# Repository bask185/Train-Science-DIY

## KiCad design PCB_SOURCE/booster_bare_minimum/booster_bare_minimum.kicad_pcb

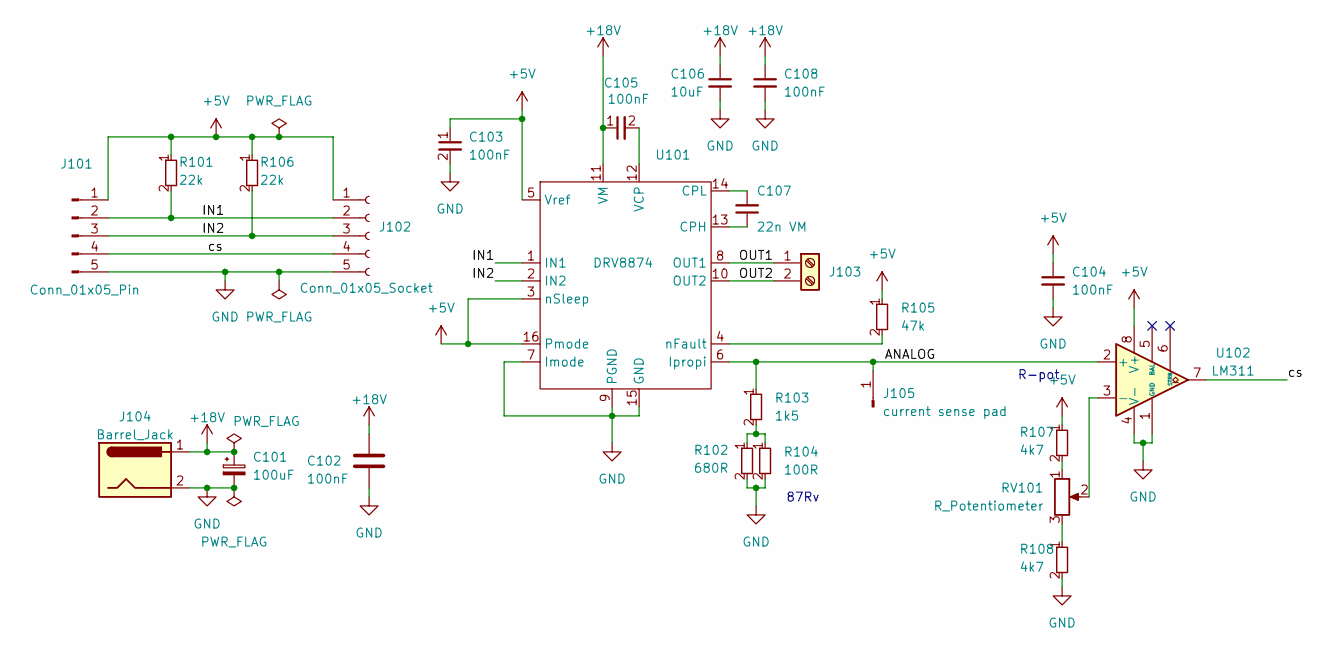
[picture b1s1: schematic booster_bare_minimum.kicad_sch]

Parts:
C101: 100uF; CP_Elec_6.3x5.9; JLCPCB Part# C494840
C102: 100nF; C_0603_1608Metric_Pad1.08x0.95mm_HandSolder; JLCPCB Part# C14663
C103, C105: 100nF; C_0603_1608Metric; JLCPCB Part# C14663
C104, C108: 100nF; C_0402_1005Metric_Pad0.74x0.62mm_HandSolder; LCSC Part # C307331
C106: 10uF; C_1206_3216Metric; LCSC Part # C13585
C107: 22n VM; C_0402_1005Metric_Pad0.74x0.62mm_HandSolder; LCSC Part # C1532
J101: Conn_01x05_Pin; PinHeader_1x05_P2.54mm_Horizontal
J102: Conn_01x05_Socket; PinSocket_1x05_P2.54mm_Horizontal
J103: Screw_Terminal_01x02; PhoenixContact_MC_1,5_2-G-3.5_1x02_P3.50mm_Horizontal; JLCPCB Part# C2840336
J104: Barrel_Jack; BarrelJack_GCT_DCJ200-10-A_Horizontal; JLCPCB Part# C7428747
J105: current sense pad; SolderWirePad_1x01_SMD_1x2mm
R101, R106: 22k; R_0603_smalltext; JLCPCB Part# C31850
R102: 680R; R_0603_smalltext; JLCPCB Part# C17798
R103: 1k5; R_0603_smalltext; JLCPCB Part# C22843
R104: 100R; R_0603_smalltext; JLCPCB Part# C22775
R105: 47k; R_0603_smalltext; JLCPCB Part# C25819
R107, R108: 4k7; R_0603_smalltext; JLCPCB Part# C23162
RV101: R_Potentiometer; Potentiometer_Bourns_TC33X_Vertical; JLCPCB Part# C145161
U101: DRV8874; HTSSOP-16-1EP_4.4x5mm_P0.65mm_EP3.4x5mm; JLCPCB Part# C1855818
U102: LM311; SOP-8_3.9x4.9mm_P1.27mm; JLCPCB Part# C434495

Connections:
+5V: C103.1, C104.1, J101.1, J102.1, R101.1, R105.1, R106.1, R107.1, U101.3 (nSleep), U101.5 (Vref), U101.16 (Pmode), U102.8 (V+)
+18V: C101.1, C102.2, C105.1, C106.1, C108.1, J104.1, U101.11 (VM)
/ANALOG: J105.1, R103.1, U101.6 (Ipropi), U102.2 (+)
/IN1: J101.2, J102.2, R101.2, U101.1 (IN1)
/IN2: J101.3, J102.3, R106.2, U101.2 (IN2)
/OUT1: J103.1, U101.8 (OUT1)
/OUT2: J103.2, U101.10 (OUT2)
/cs: J101.4, J102.4, U102.7
GND: C101.2, C102.1, C103.2, C104.2, C106.2, C108.2, J101.5, J102.5, J104.2, R102.2, R104.2, R108.2, U101.7 (Imode), U101.9 (PGND), U101.15 (GND), U101.17 (GND), U102.1 (GND), U102.4 (V-)
unnamed: R102.1, R103.2, R104.1
unnamed: R107.2, RV101.1
unnamed: R108.1, RV101.3
unnamed: C107.1, U101.13 (CPH)
unnamed: C107.2, U101.14 (CPL)
unnamed: C105.2, U101.12 (VCP)
unnamed: R105.2, U101.4 (nFault)
unnamed: RV101.2, U102.3 (-)

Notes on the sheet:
87Rv
R-pot

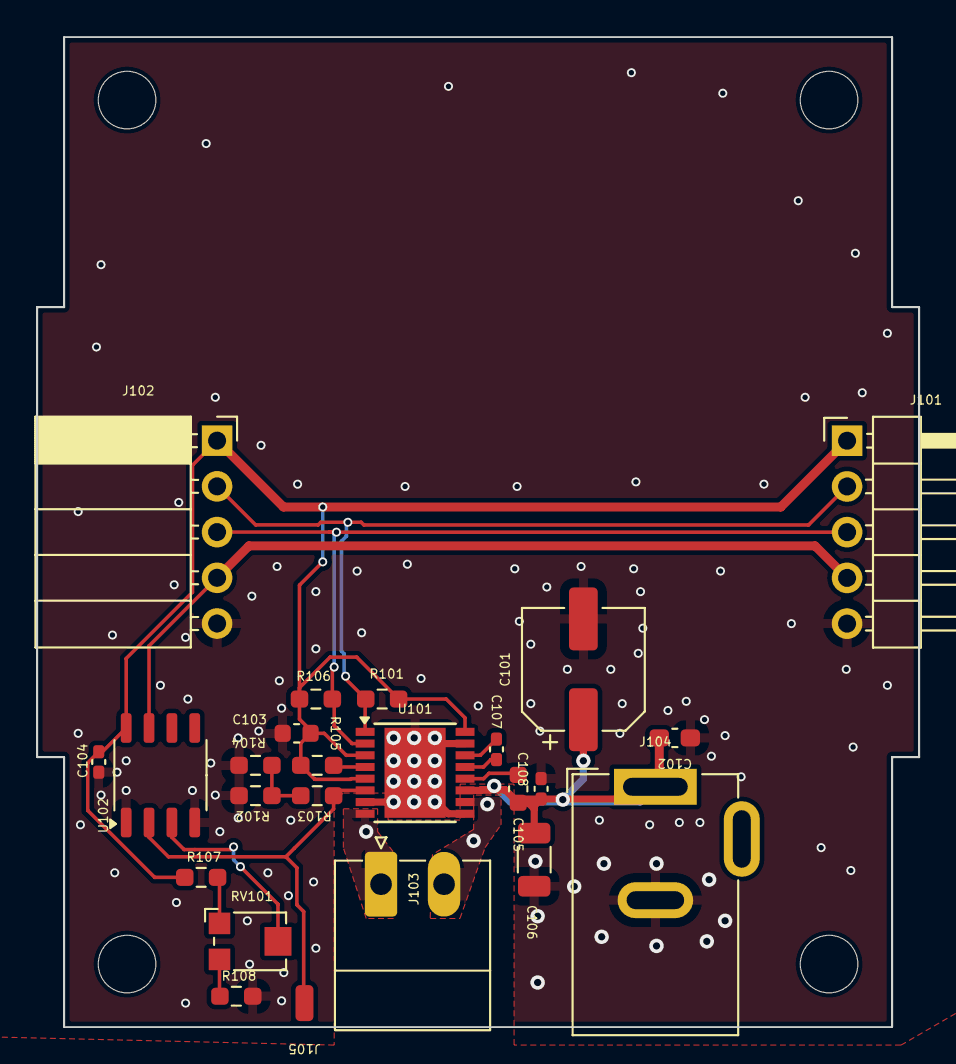
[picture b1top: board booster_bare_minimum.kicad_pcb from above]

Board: 2 copper layers, 49.0 x 55.0 mm, 24 parts (0 on the bottom side), 17 nets.

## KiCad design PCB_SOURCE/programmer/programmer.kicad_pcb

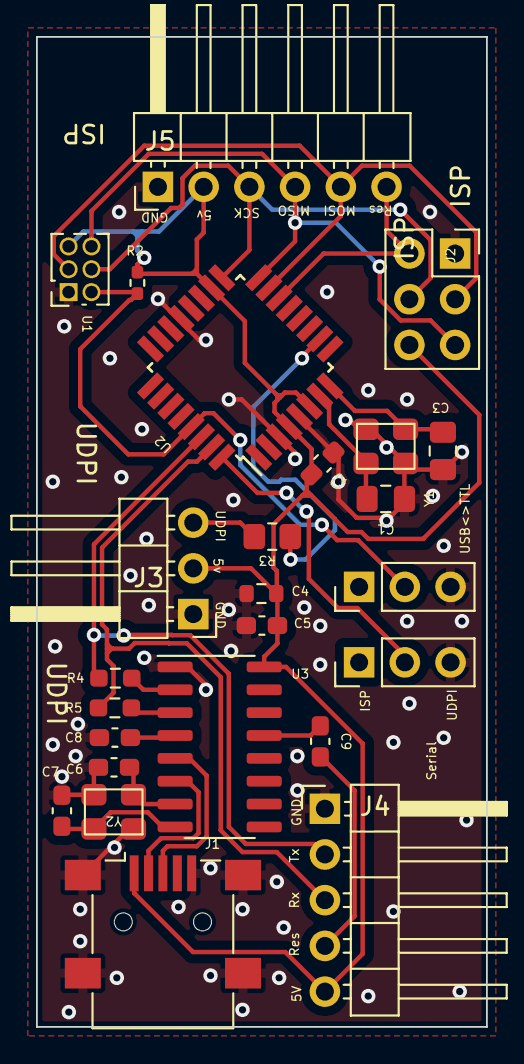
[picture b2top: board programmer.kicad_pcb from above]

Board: 2 copper layers, 25.0 x 55.0 mm, 25 parts (0 on the bottom side), 23 nets.

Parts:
C1, C3: 12pF; C_0805_2012Metric_Pad1.18x1.45mm_HandSolder
C2, C5, C8, C9: 100nF; C_0603_1608Metric_Pad1.08x0.95mm_HandSolder
C4: 10uF; R_0603_1608Metric
C6, C7: 22pF; C_0603_1608Metric_Pad1.08x0.95mm_HandSolder
J1: USB_B_Mini; USB_Mini-B_Lumberg_2486_01_Horizontal
J2: 2x3 ISP; PinSocket_2x03_P2.54mm_Vertical
J3: UDPI; PinHeader_1x03_P2.54mm_Horizontal
J4: USB_TTL; PinHeader_1x05_P2.54mm_Horizontal
J5: 1x6 ISP; PinHeader_1x06_P2.54mm_Horizontal
R2: 10k; R_0402_1005Metric_Pad0.72x0.64mm_HandSolder
R3: 4k7; R_0805_handsolder-smalltext
R4, R5: 1k; R_0603_1608Metric_Pad0.98x0.95mm_HandSolder
SW2, SW101: SW_SPDT; PinHeader_1x03_P2.54mm_Vertical
U1: HEADER_3x2; PinSocket_2x03_P1.27mm_Vertical
U2: ATmega328-A; TQFP-32_7x7mm_P0.8mm
U3: CH340G; SOIC-16_3.9x9.9mm_P1.27mm
Y1: Crystal_GND2; crystal_arduino
Y2: Crystal; crystal_arduino

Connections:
+5V: C2.2, C4.1, C5.1, J1.1 (VBUS), J2.6, J3.2, J4.5, J5.2, R2.1, U1.5, U2.4 (VCC), U2.6 (VCC), U2.18 (AVCC), U3.16 (VCC)
/MISO: J2.5, J5.4, U1.6, U2.16 (PB4)
/MOSI: J2.3, J5.5, U1.3, U2.15 (PB3)
/RESET: J2.2, J5.6, U2.14 (PB2)
/RX: J4.2, R4.2, U2.30 (PD0)
/SCK: J2.4, J5.3, U1.4, U2.17 (PB5)
/TX: J4.3, R5.1, U2.31 (PD1)
/UDPI: J3.3, R3.2
/USB_RESET: C9.2, J4.4
/X1: C1.2, U2.7 (XTAL1/PB6), Y1.1
/X2: C3.2, U2.8 (XTAL2/PB7), Y1.3
/our_reset: R2.2, SW101.2 (B), U1.2, U2.29 (~RESET/PC6)
GND: C1.1, C2.1, C3.1, C4.2, C5.2, C6.2, C7.2, C8.1, J1.5 (GND), J1.6 (Shield), J2.1, J3.1, J4.1, J5.1, SW2.3 (C), SW101.3 (C), U1.1, U2.3 (GND), U2.5 (GND), U2.21 (GND), U3.1 (GND), Y1.2 (GND), Y1.4 (GND), Y2.2 (GND), Y2.4 (GND)
unnamed: J1.3 (D+), U3.5 (UD+)
unnamed: J1.2 (D-), U3.6 (UD-)
unnamed: SW2.2 (B), U2.32 (PD2)
unnamed: R3.1, U2.10 (PD6)
unnamed: R5.2, U3.3 (RXD)
unnamed: R4.1, U3.2 (TXD)
unnamed: C8.2, U3.4 (V3)
unnamed: C6.1, U3.7 (XI), Y2.1
unnamed: C7.1, U3.8 (XO), Y2.3
unnamed: C9.1, U3.13 (~DTR)

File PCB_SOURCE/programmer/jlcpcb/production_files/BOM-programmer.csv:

Comment,Designator,Footprint,LCSC
Crystal_GND2,Y1,crystal_arduino,C13738
CH340G,U3,SOIC-16_3.9x9.9mm_P1.27mm,C14267
100nF,"C2,C5,C8,C9",C_0603_1608Metric_Pad1.08x0.95mm_HandSolder,C14663
ATmega328-A,U2,TQFP-32_7x7mm_P0.8mm,C14877
22pF,"C6,C7",C_0603_1608Metric_Pad1.08x0.95mm_HandSolder,C1653
4k7,R3,R_0805_handsolder-smalltext,C17673
12pF,C3,C_0805_2012Metric_Pad1.18x1.45mm_HandSolder,C1792
1k,"R4,R5",R_0603_1608Metric_Pad0.98x0.95mm_HandSolder,C21190
10k,R2,R_0402_1005Metric_Pad0.72x0.64mm_HandSolder,C25744
USB_B_Mini,J1,USB_Mini-B_Lumberg_2486_01_Horizontal,C2681563
Crystal,Y2,crystal_arduino,C9002
10uF,C4,R_0603_1608Metric,C96446
SW_SPDT,SW101,PinHeader_1x03_P2.54mm_Vertical,
SW_SPDT,SW2,PinHeader_1x03_P2.54mm_Vertical,
HEADER_3x2,U1,PinSocket_2x03_P1.27mm_Vertical,
1x6 ISP,J5,PinHeader_1x06_P2.54mm_Horizontal,
12pF,C1,C_0805_2012Metric_Pad1.18x1.45mm_HandSolder,
UDPI,J3,PinHeader_1x03_P2.54mm_Horizontal,
2x3 ISP,J2,PinSocket_2x03_P2.54mm_Vertical,
USB_TTL,J4,PinHeader_1x05_P2.54mm_Horizontal,

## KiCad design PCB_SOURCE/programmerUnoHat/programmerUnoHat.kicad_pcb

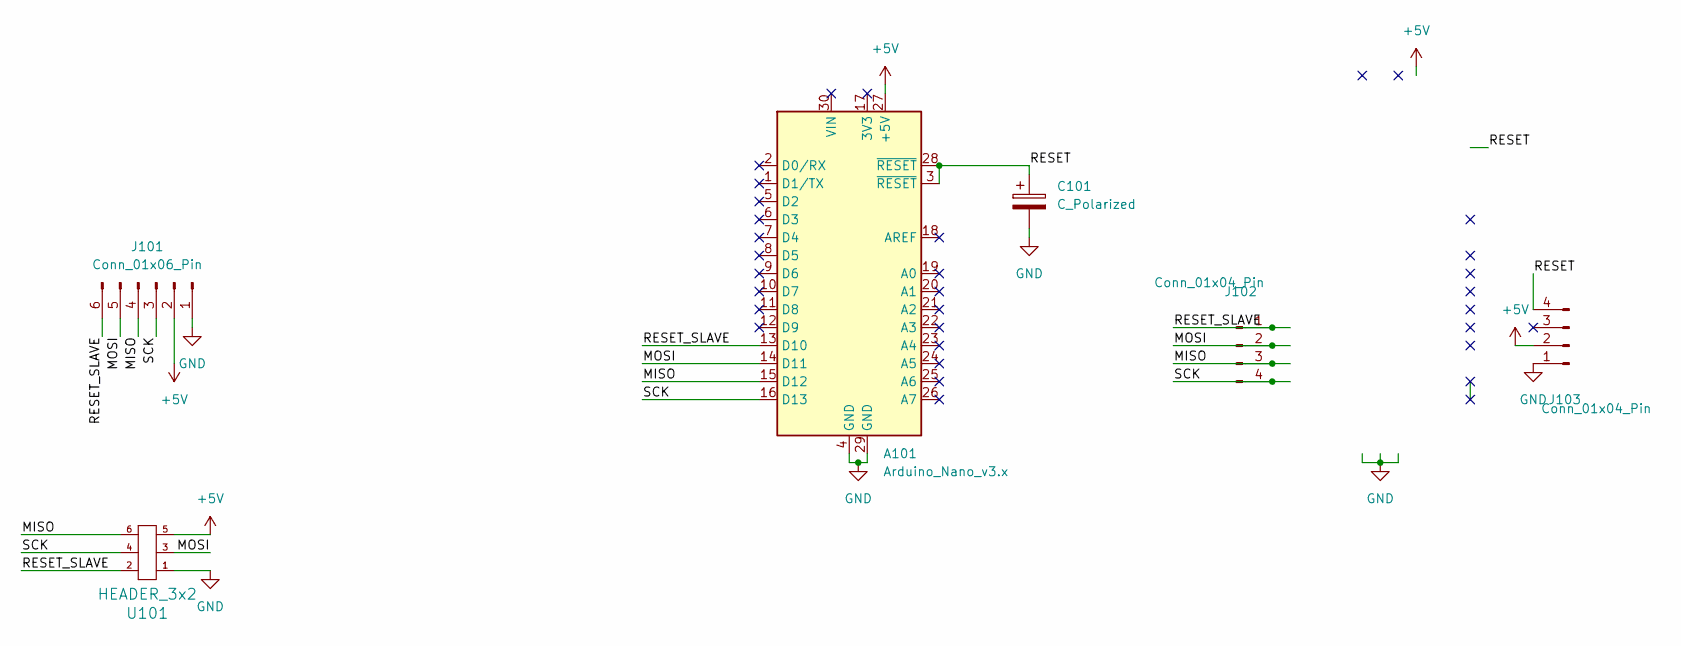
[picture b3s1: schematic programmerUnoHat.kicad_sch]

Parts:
A101: Arduino_Nano_v3.x; Arduino_Nano
C101: C_Polarized; CP_Radial_D6.3mm_P2.50mm
J101: Conn_01x06_Pin; PinHeader_1x06_P2.54mm_Vertical
J102, J103: Conn_01x04_Pin; PinHeader_1x04_P2.54mm_Vertical
U101: HEADER_3x2; PinSocket_2x03_P1.27mm_Vertical

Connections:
+5V: A101.27 (+5V), J101.2, J103.2, U101.5
/MISO: A101.15 (D12), J101.4, J102.3, U101.6
/MOSI: A101.14 (D11), J101.5, J102.2, U101.3
/RESET: A101.3 (~RESET), A101.28 (~RESET), C101.1, J103.4
/RESET_SLAVE: A101.13 (D10), J101.6, J102.1, U101.2
/SCK: A101.16 (D13), J101.3, J102.4, U101.4
GND: A101.4 (GND), A101.29 (GND), C101.2, J101.1, J103.1, U101.1

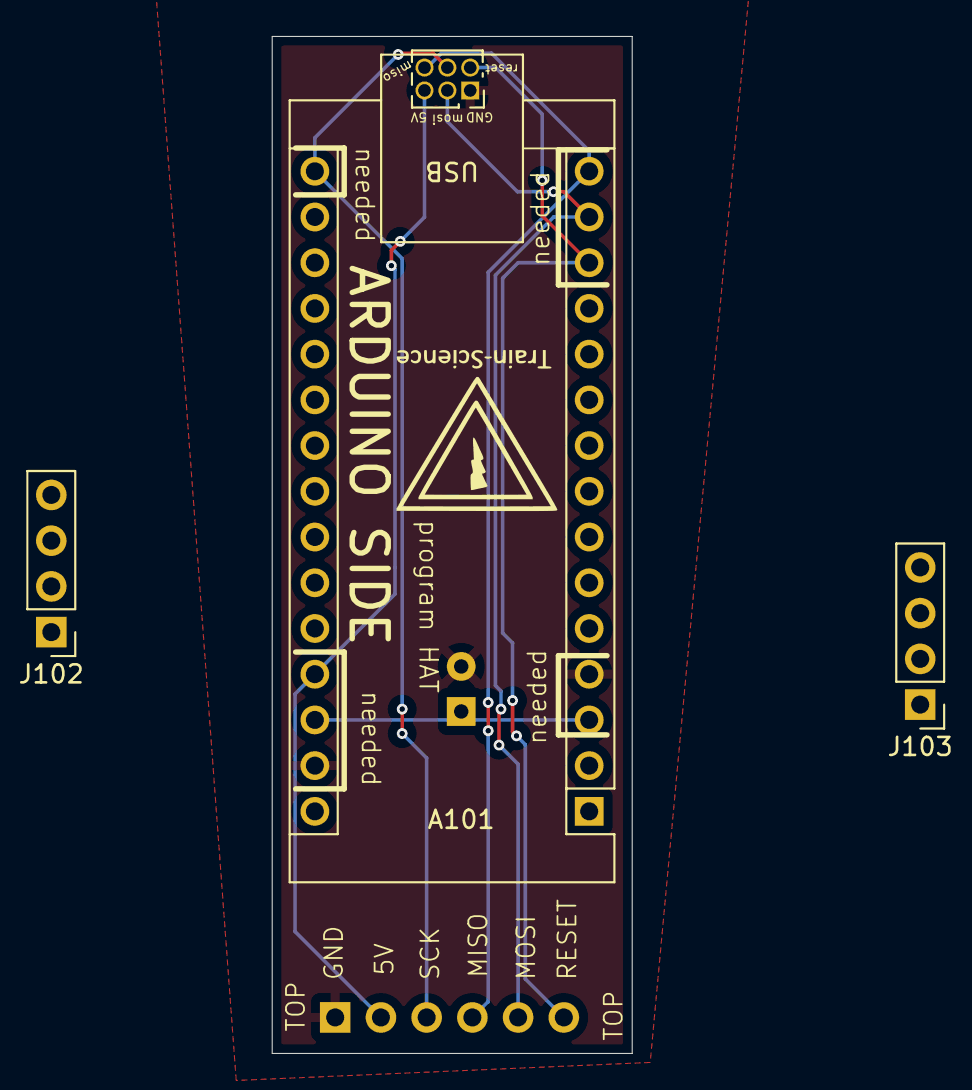
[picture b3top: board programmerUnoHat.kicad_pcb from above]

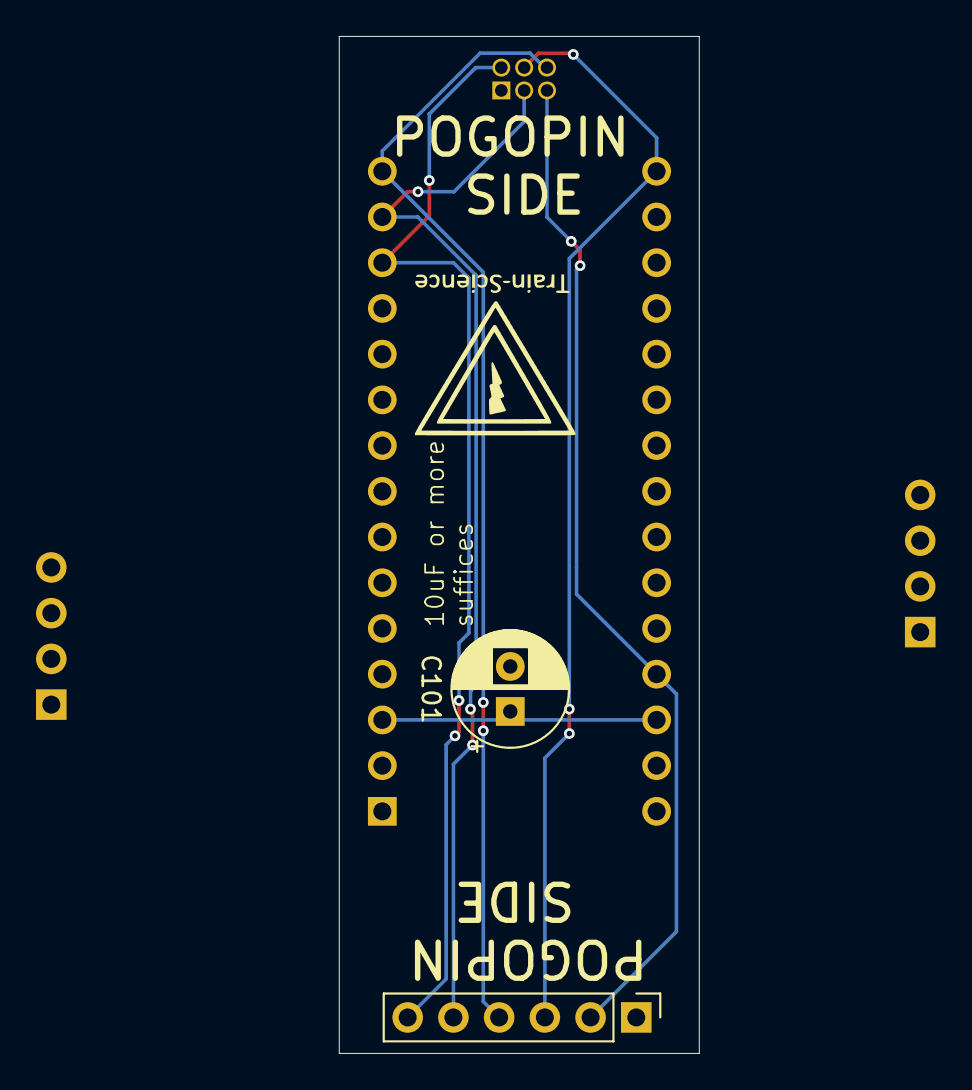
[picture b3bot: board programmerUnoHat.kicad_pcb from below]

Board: 2 copper layers, 20.0 x 56.5 mm, 6 parts (2 on the bottom side), 7 nets.

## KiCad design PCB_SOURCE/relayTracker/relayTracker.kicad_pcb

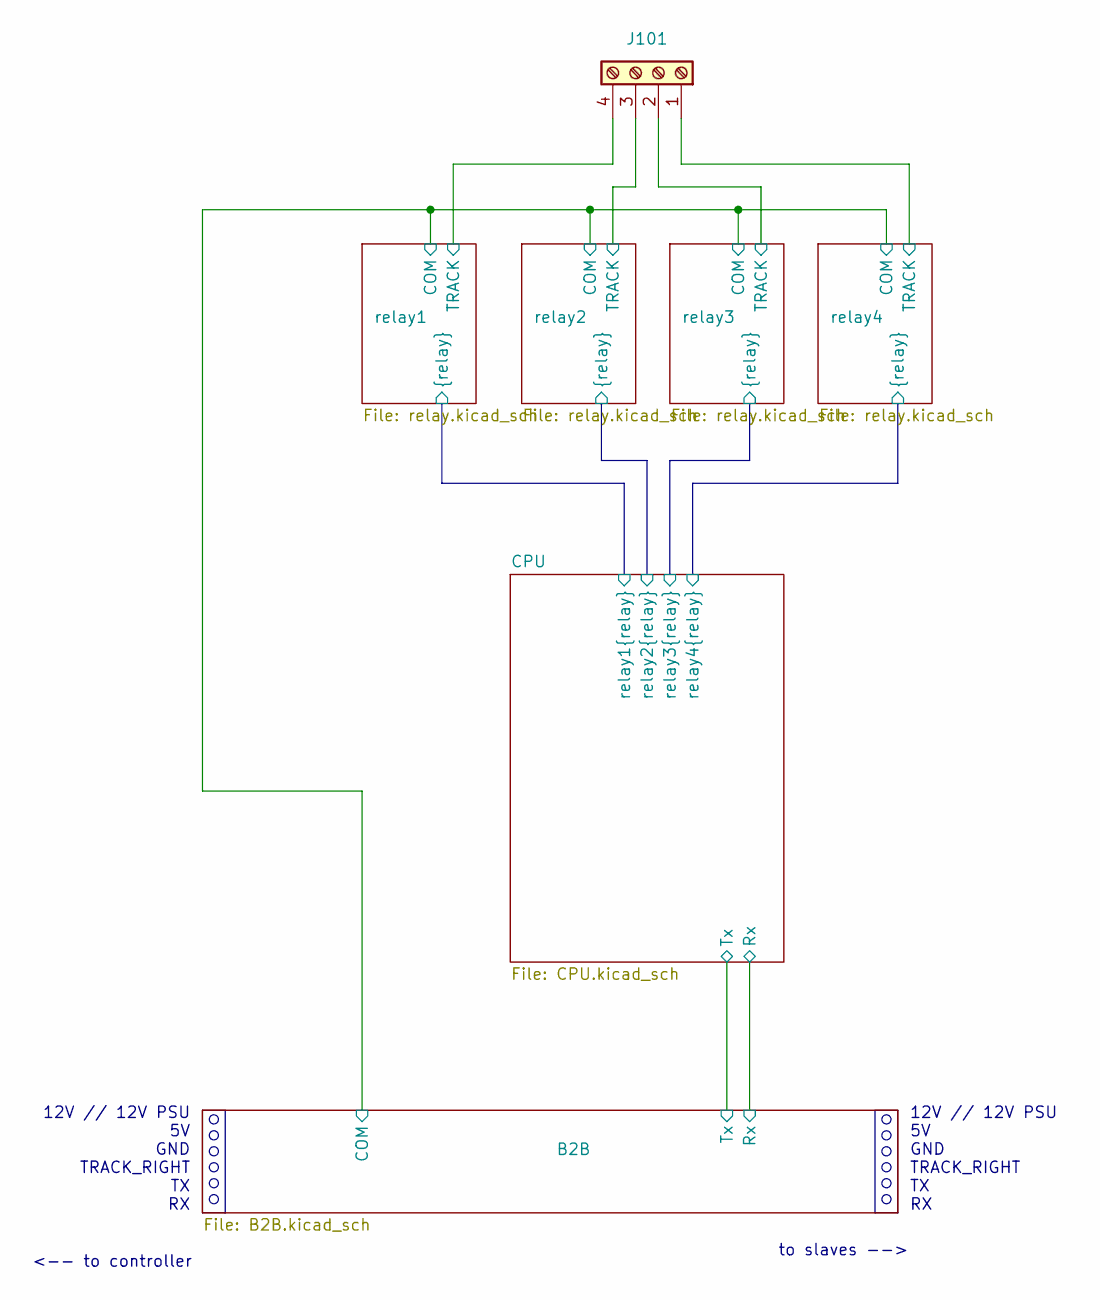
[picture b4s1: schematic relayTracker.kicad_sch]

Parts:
J101: Screw_Terminal_01x04; TerminalBlock_Phoenix_MKDS-1,5-4-5.08_1x04_P5.08mm_Horizont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

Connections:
/relay1/TRACK: J101.4; also elsewhere on the board
/relay2/TRACK: J101.3; also elsewhere on the board
/relay3/TRACK: J101.2; also elsewhere on the board
/relay4/TRACK: J101.1; also elsewhere on the board

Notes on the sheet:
12V // 12V PSU 5V GND TRACK_RIGHT TX RX
<-- to controller
to slaves -->

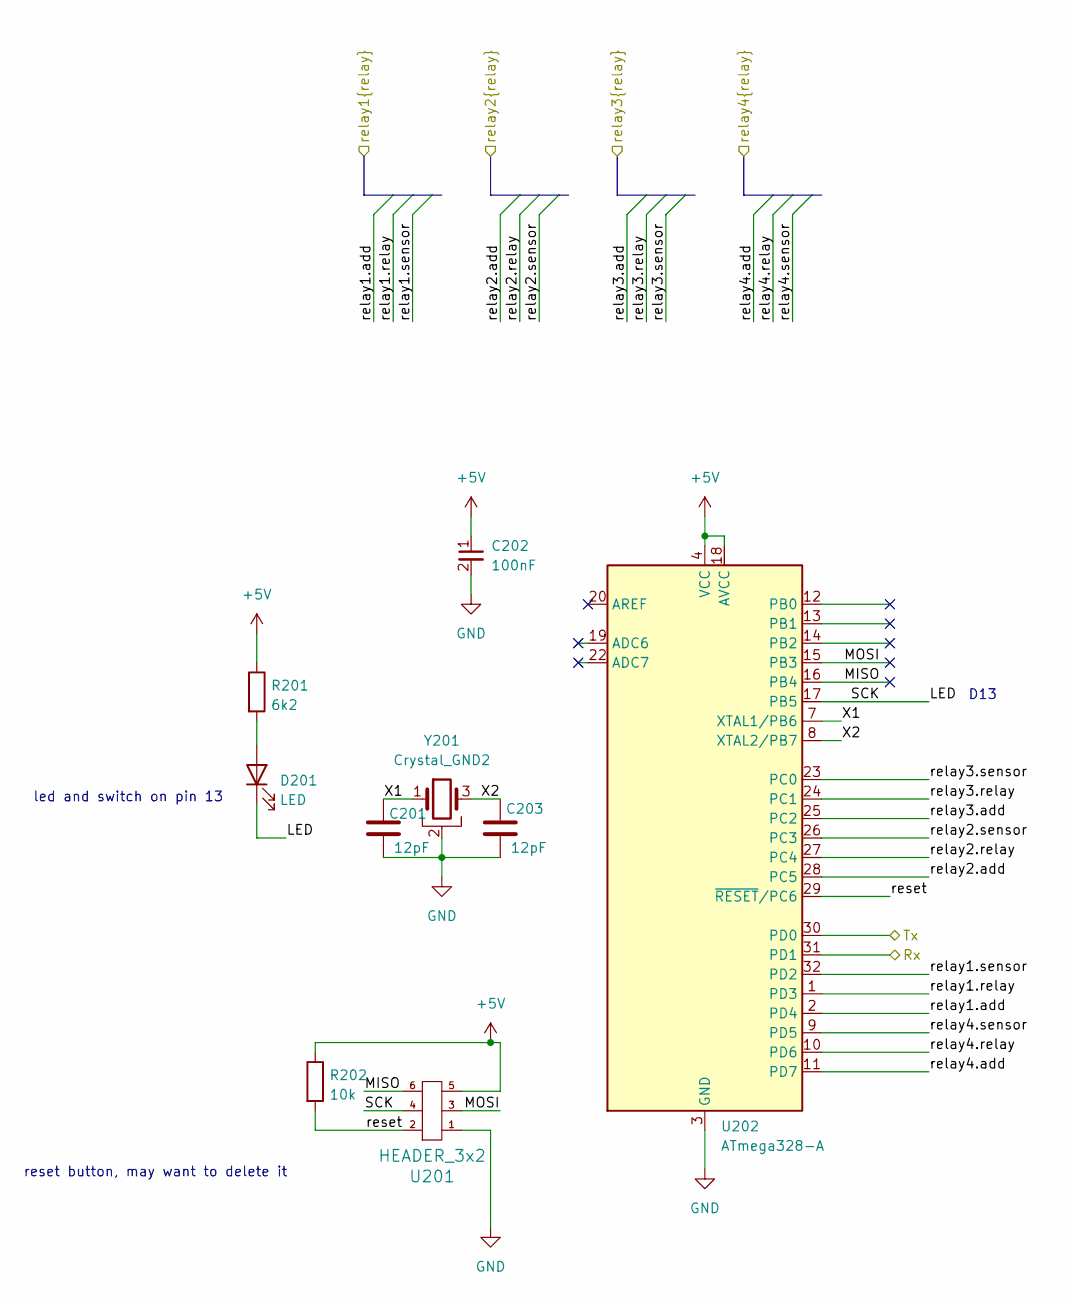
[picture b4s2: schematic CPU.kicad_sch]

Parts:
C201, C203: 12pF; C_0603_1608Metric; JLCPCB Part# C38523
C202: 100nF; C_0402_1005Metric; JLCPCB Part# C307331
D201: LED; LED_0805_2012Metric_Pad1.15x1.40mm_HandSolder; JLCPCB Part# C84256
R201: 6k2; R_0603_1608Metric_Pad0.98x0.95mm_HandSolder; JLCPCB Part# C4260
R202: 10k; R_0402_1005Metric_Pad0.72x0.64mm_HandSolder; JLCPCB Part# C25744
U201: HEADER_3x2; PinSocket_2x03_P1.27mm_Vertical
U202: ATmega328-A; TQFP-32_7x7mm_P0.8mm; JLCPCB Part# C14877
Y201: Crystal_GND2; crystal_arduino; JLCPCB Part# C13738

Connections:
+5V: C202.1, R201.1, R202.1, U201.5, U202.4 (VCC), U202.6 (VCC), U202.18 (AVCC); also elsewhere on the board
/B2B/Rx: U202.31 (PD1); also elsewhere on the board
/B2B/Tx: U202.30 (PD0); also elsewhere on the board
/CPU/LED: D201.1 (K), U201.4, U202.17 (PB5)
/CPU/MISO: U201.6, U202.16 (PB4)
/CPU/MOSI: U201.3, U202.15 (PB3)
/CPU/X1: C201.2, U202.7 (XTAL1/PB6), Y201.1
/CPU/X2: C203.2, U202.8 (XTAL2/PB7), Y201.3
/CPU/relay1.add: U202.2 (PD4); also elsewhere on the board
/CPU/relay1.relay: U202.1 (PD3); also elsewhere on the board
/CPU/relay1.sensor: U202.32 (PD2); also elsewhere on the board
/CPU/relay2.add: U202.28 (PC5); also elsewhere on the board
/CPU/relay2.relay: U202.27 (PC4); also elsewhere on the board
/CPU/relay2.sensor: U202.26 (PC3); also elsewhere on the board
/CPU/relay3.add: U202.25 (PC2); also elsewhere on the board
/CPU/relay3.relay: U202.24 (PC1); also elsewhere on the board
/CPU/relay3.sensor: U202.23 (PC0); also elsewhere on the board
/CPU/relay4.add: U202.11 (PD7); also elsewhere on the board
/CPU/relay4.relay: U202.10 (PD6); also elsewhere on the board
/CPU/relay4.sensor: U202.9 (PD5); also elsewhere on the board
/CPU/reset: R202.2, U201.2, U202.29 (~RESET/PC6)
GND: C201.1, C202.2, C203.1, U201.1, U202.3 (GND), U202.5 (GND), U202.21 (GND), Y201.2 (GND), Y201.4 (GND); also elsewhere on the board
unnamed: D201.2 (A), R201.2

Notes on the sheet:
reset button, may want to delete it
led and switch on pin 13
D13

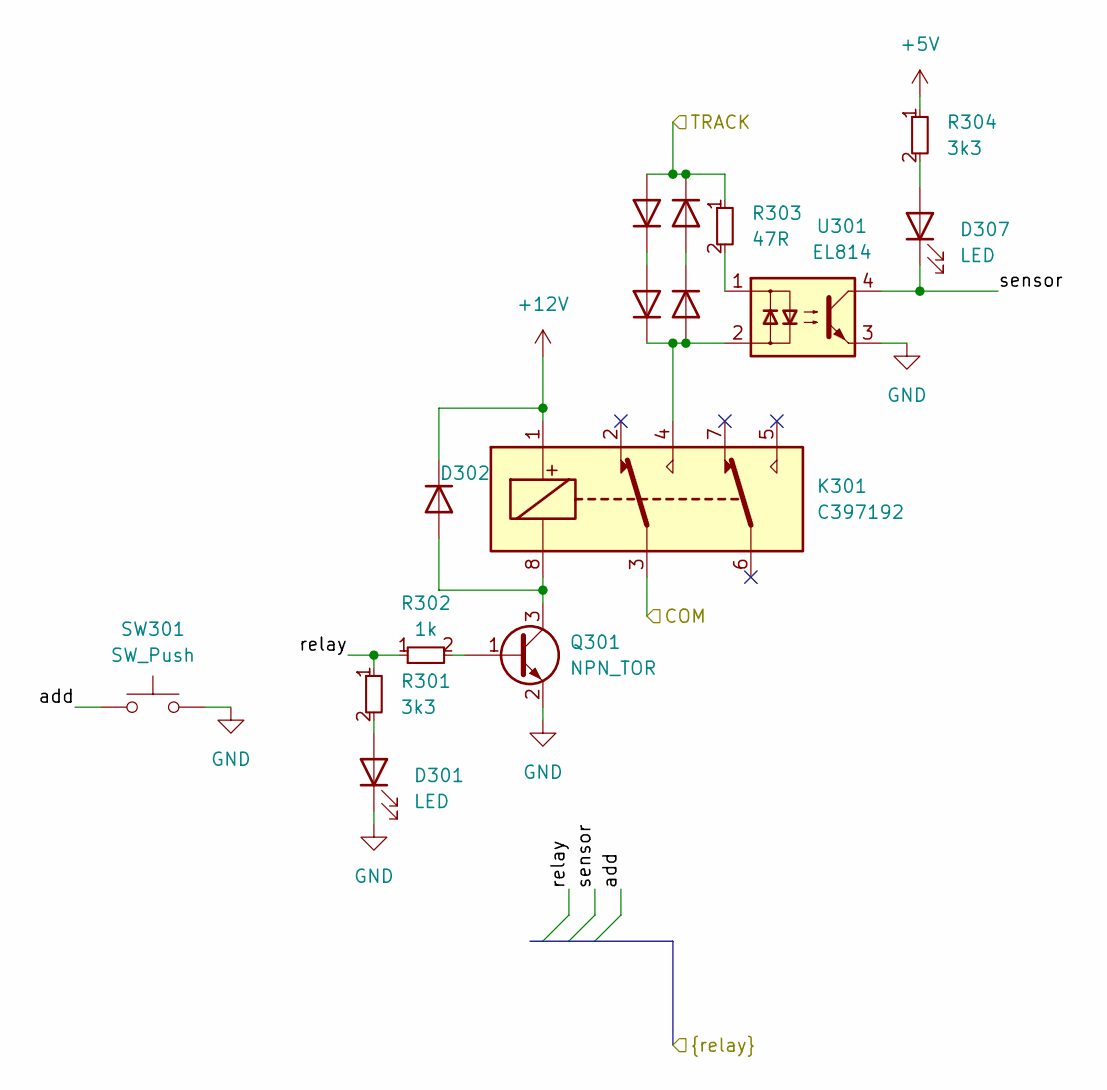
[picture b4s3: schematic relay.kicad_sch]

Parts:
D301, D307: LED; LED_0805_2012Metric_Pad1.15x1.40mm_HandSolder; JLCPCB Part# C2296
D302: 1N4148WS; D_SOD-323; JLCPCB Part# C2128
D303, D304, D305, D306: SS53; D_SMA; JLCPCB Part# C8678
K301: G6K-2F-Y-TR DC12; Relay_DPDT_Omron_G6K-2F-Y; JLCPCB Part# C397192
Q301: NPN_TOR; SOT-23; JLCPCB Part# C2145
R301, R304: 3k3; R_0603_smalltext; JLCPCB Part# C22978
R302: 1k; R_0603_smalltext; JLCPCB Part# C21190
R303: 47R; R_0603_smalltext; JLCPCB Part# C23182
SW301: SW_Push; tactile_SMD_6mm; JLCPCB Part# C294569
U301: EL814; SMDIP-4_W9.53mm; JLCPCB Part# C500388

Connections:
+5V: R304.1; also elsewhere on the board
+12V: D302.1 (K), K301.1; also elsewhere on the board
/B2B/COM: K301.3; also elsewhere on the board
/CPU/relay1.add: SW301.1; also elsewhere on the board
/CPU/relay1.relay: R301.1, R302.1; also elsewhere on the board
/CPU/relay1.sensor: D307.1 (K), U301.4; also elsewhere on the board
/relay1/TRACK: D303.2 (A), D305.1 (K), R303.1; also elsewhere on the board
GND: D301.1 (K), Q301.2 (E), SW301.2, U301.3; also elsewhere on the board
unnamed: D301.2 (A), R301.2
unnamed: D302.2 (A), K301.8, Q301.3 (C)
unnamed: D303.1 (K), D304.2 (A)
unnamed: D304.1 (K), D306.2 (A), K301.4, U301.2
unnamed: D305.2 (A), D306.1 (K)
unnamed: D307.2 (A), R304.2
unnamed: Q301.1 (B), R302.2
unnamed: R303.2, U301.1

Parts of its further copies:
D501, D507, D601, D607, D701, D707: LED; LED_0805_2012Metric_Pad1.15x1.40mm_HandSolder; JLCPCB Part# C2296
D502, D602, D702: 1N4148WS; D_SOD-323; JLCPCB Part# C2128
D503, D504, D505, D506, D603, D604, D605, D606, D703, D704, D705, D706: SS53; D_SMA; JLCPCB Part# C8678
K501, K601, K701: G6K-2F-Y-TR DC12; Relay_DPDT_Omron_G6K-2F-Y; JLCPCB Part# C397192
Q501, Q601, Q701: NPN_TOR; SOT-23; JLCPCB Part# C2145
R501, R504, R601, R604, R701, R704: 3k3; R_0603_smalltext; JLCPCB Part# C22978
R502, R602, R702: 1k; R_0603_smalltext; JLCPCB Part# C21190
R503, R603, R703: 47R; R_0603_smalltext; JLCPCB Part# C23182
SW501, SW601, SW701: SW_Push; tactile_SMD_6mm; JLCPCB Part# C294569
U501, U601, U701: EL814; SMDIP-4_W9.53mm; JLCPCB Part# C500388

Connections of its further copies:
+5V: R504.1, R604.1, R704.1; also elsewhere on the board
+12V: D502.1 (K), D602.1 (K), D702.1 (K), K501.1, K601.1, K701.1; also elsewhere on the board
/B2B/COM: K501.3, K601.3, K701.3; also elsewhere on the board
/CPU/relay2.add: SW501.1; also elsewhere on the board
/CPU/relay2.relay: R501.1, R502.1; also elsewhere on the board
/CPU/relay2.sensor: D507.1 (K), U501.4; also elsewhere on the board
/CPU/relay3.add: SW601.1; also elsewhere on the board
/CPU/relay3.relay: R601.1, R602.1; also elsewhere on the board
/CPU/relay3.sensor: D607.1 (K), U601.4; also elsewhere on the board
/CPU/relay4.add: SW701.1; also elsewhere on the board
/CPU/relay4.relay: R701.1, R702.1; also elsewhere on the board
/CPU/relay4.sensor: D707.1 (K), U701.4; also elsewhere on the board
/relay2/TRACK: D503.2 (A), D505.1 (K), R503.1; also elsewhere on the board
/relay3/TRACK: D603.2 (A), D605.1 (K), R603.1; also elsewhere on the board
/relay4/TRACK: D703.2 (A), D705.1 (K), R703.1; also elsewhere on the board
GND: D501.1 (K), D601.1 (K), D701.1 (K), Q501.2 (E), Q601.2 (E), Q701.2 (E), SW501.2, SW601.2, SW701.2, U501.3, U601.3, U701.3; also elsewhere on the board
unnamed: D501.2 (A), R501.2
unnamed: D502.2 (A), K501.8, Q501.3 (C)
unnamed: D503.1 (K), D504.2 (A)
unnamed: D504.1 (K), D506.2 (A), K501.4, U501.2
unnamed: D505.2 (A), D506.1 (K)
unnamed: D507.2 (A), R504.2
unnamed: D601.2 (A), R601.2
unnamed: D602.2 (A), K601.8, Q601.3 (C)
unnamed: D603.1 (K), D604.2 (A)
unnamed: D604.1 (K), D606.2 (A), K601.4, U601.2
unnamed: D605.2 (A), D606.1 (K)
unnamed: D607.2 (A), R604.2
unnamed: D701.2 (A), R701.2
unnamed: D702.2 (A), K701.8, Q701.3 (C)
unnamed: D703.1 (K), D704.2 (A)
unnamed: D704.1 (K), D706.2 (A), K701.4, U701.2
unnamed: D705.2 (A), D706.1 (K)
unnamed: D707.2 (A), R704.2
unnamed: Q501.1 (B), R502.2
unnamed: Q601.1 (B), R602.2
unnamed: Q701.1 (B), R702.2
unnamed: R503.2, U501.1
unnamed: R603.2, U601.1
unnamed: R703.2, U701.1

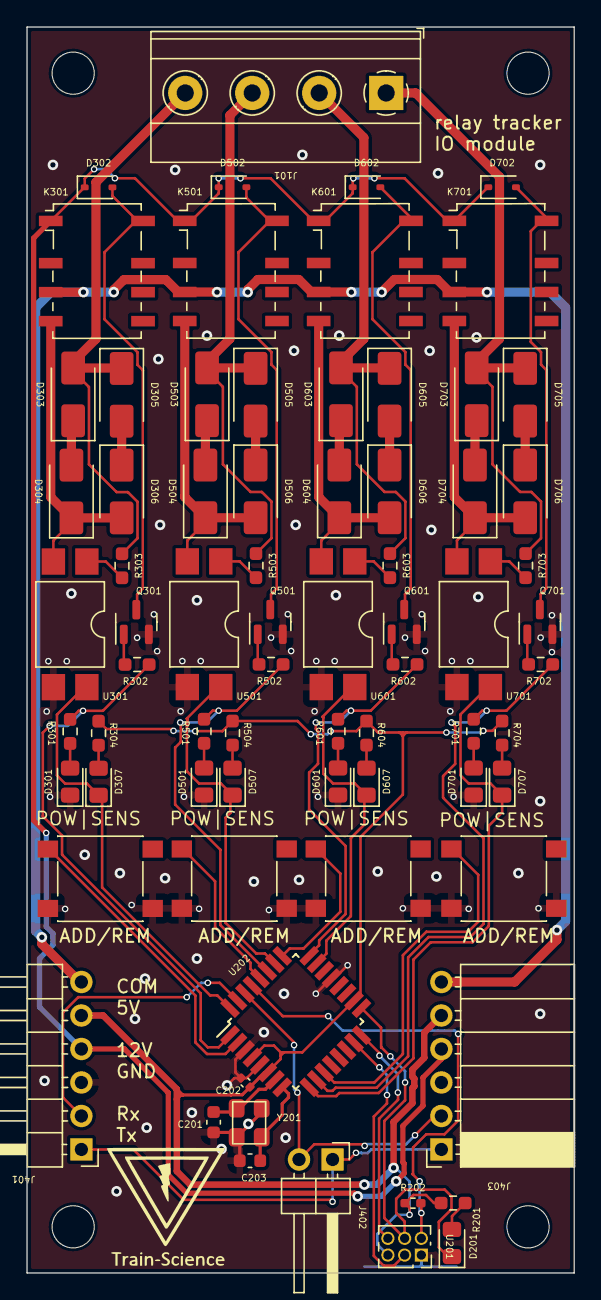
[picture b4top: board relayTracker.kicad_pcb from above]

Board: 2 copper layers, 41.5 x 94.5 mm, 73 parts (0 on the bottom side), 62 nets.

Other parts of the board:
J401: Conn_01x06_Pin; PinHeader_1x06_P2.54mm_Horizontal
J402: Conn_01x02_Pin; PinHeader_1x02_P2.54mm_Horizontal
J403: Conn_01x06_Socket; PinSocket_1x06_P2.54mm_Horizontal

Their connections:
+5V: J401.5, J403.5; also elsewhere on the board
+12V: J401.4, J403.4; also elsewhere on the board
/B2B/COM: J401.6, J403.6; also elsewhere on the board
/B2B/Rx: J401.2; also elsewhere on the board
/B2B/Tx: J402.2, J403.2; also elsewhere on the board
/B2B/TxToCentral: J401.1, J402.1, J403.1
GND: J401.3, J403.3; also elsewhere on the board
